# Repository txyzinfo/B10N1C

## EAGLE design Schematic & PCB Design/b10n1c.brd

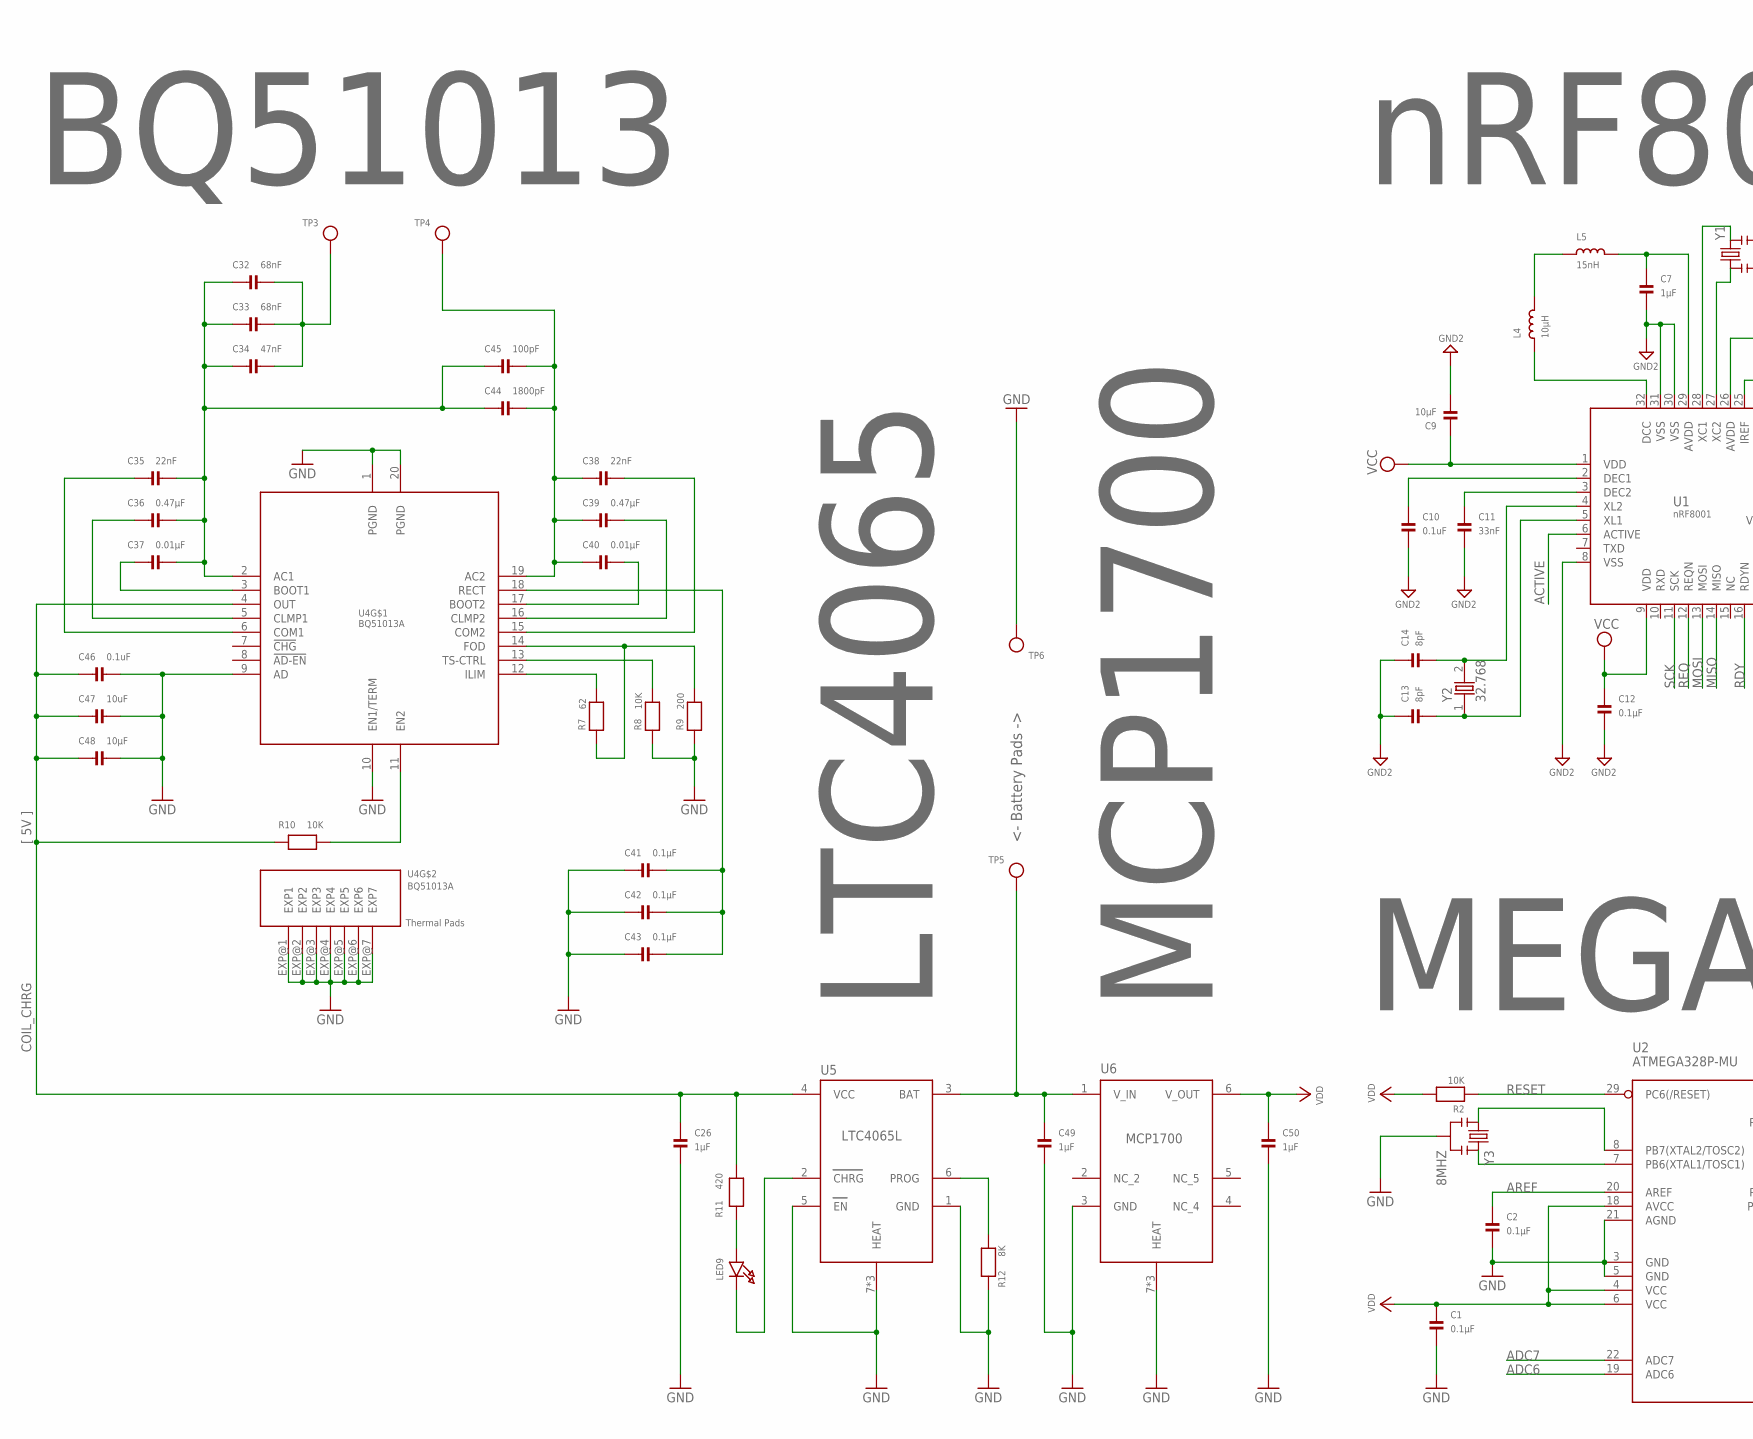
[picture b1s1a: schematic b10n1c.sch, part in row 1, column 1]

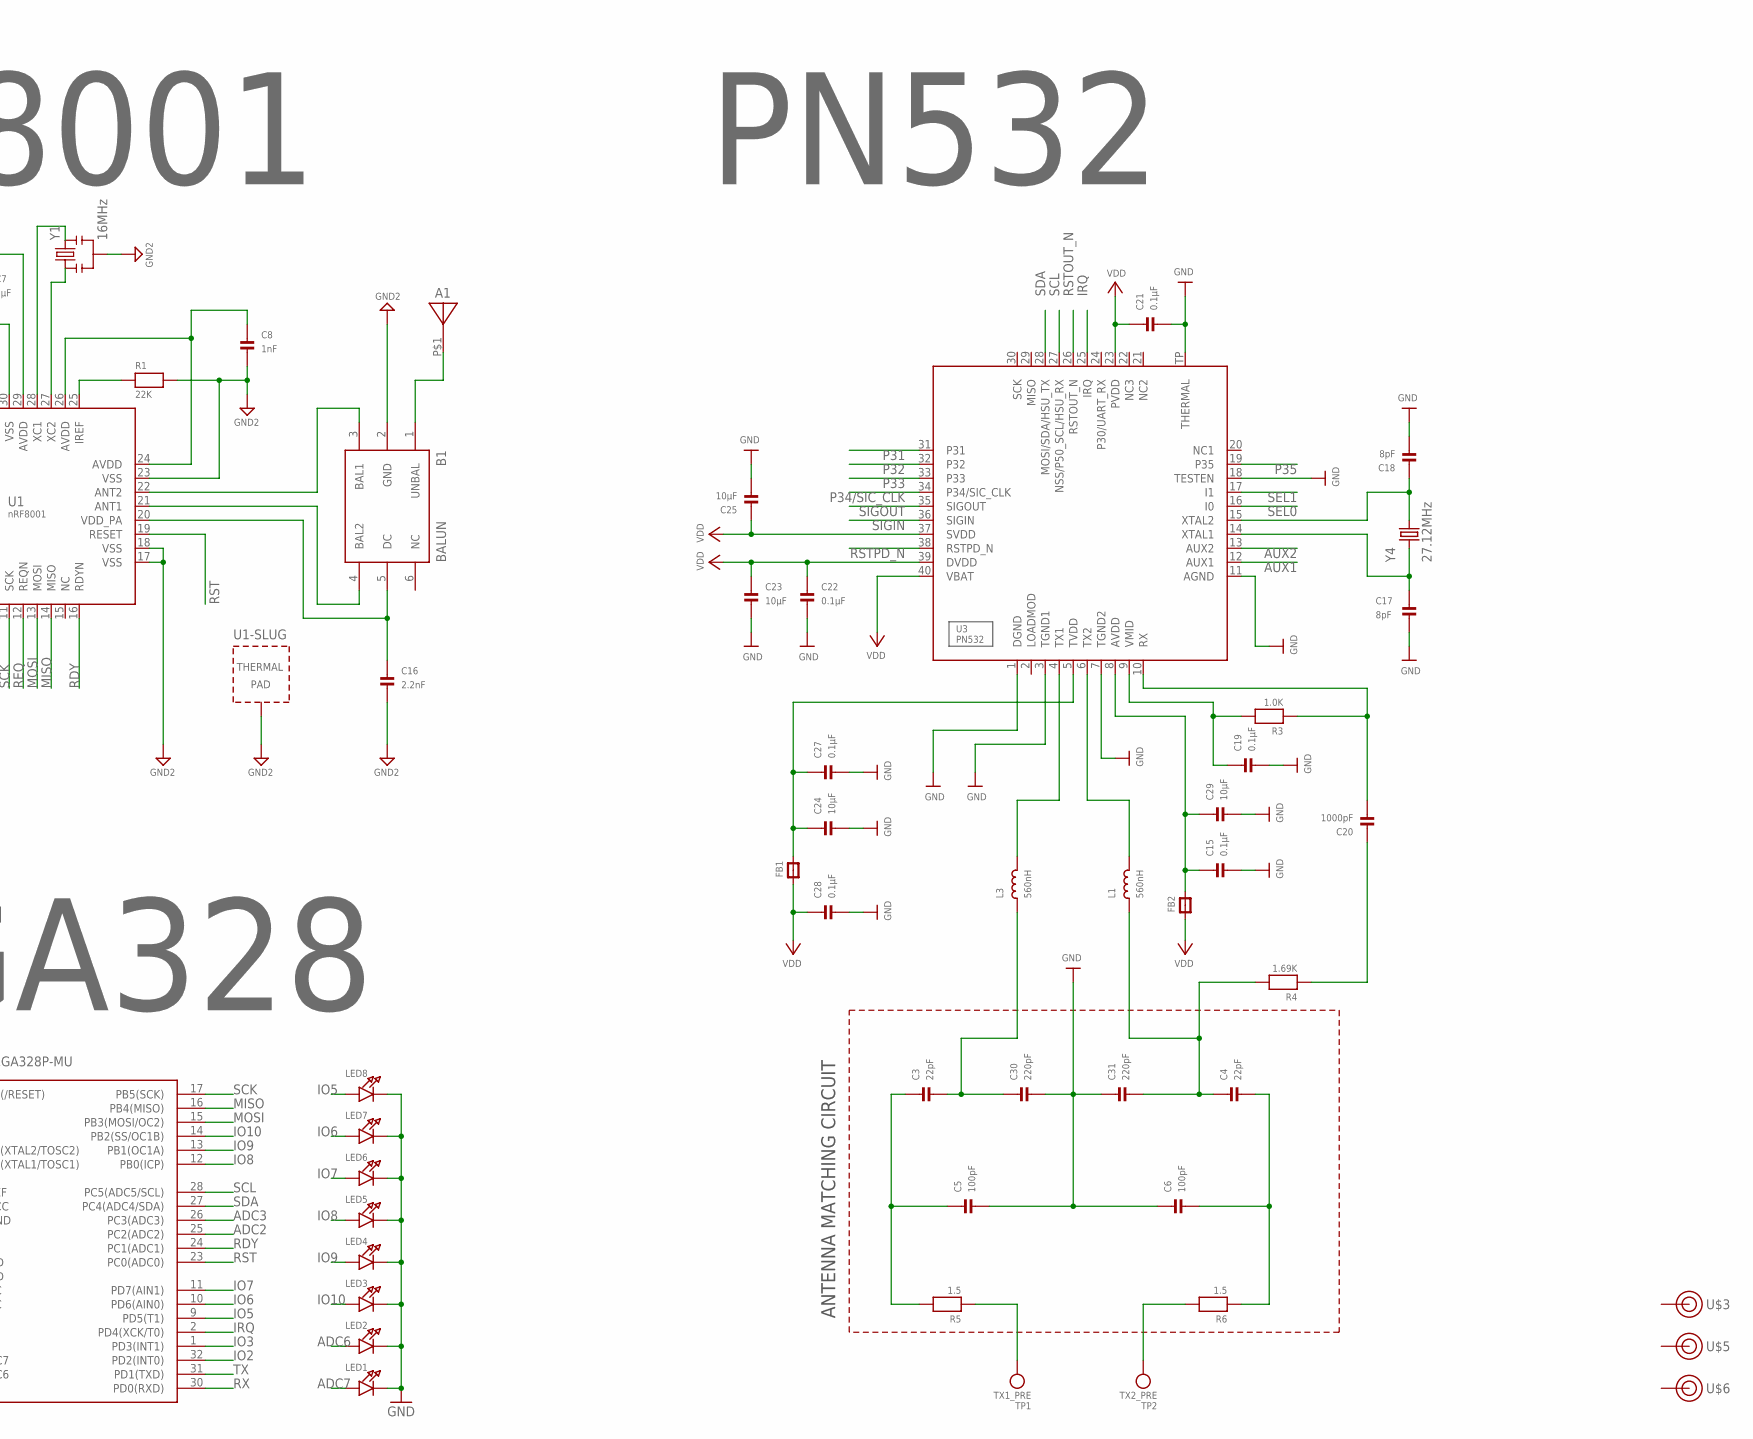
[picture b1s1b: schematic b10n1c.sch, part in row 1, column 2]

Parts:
A1: 2450AT18A100
B1: 2450BM14A0002T
C1, C2, C12, C15, C19, C21, C22, C27, C28, C41, C42, C43: 0.1µF; _0402MP
C3, C4: 22pF; _0402MP
C5, C6, C45: 100pF; _0402MP
C7, C26, C49, C50: 1µF; _0402MP
C8: 1nF; _0402MP
C9, C23, C24, C25, C29, C48: 10µF; _0402MP
C10, C46: 0.1uF; _0402MP
C11: 33nF; _0402MP
C13, C14: 8pF; _0402MP; DIGIKEY 490-5880-1-ND
C16: 2.2nF; _0402MP
C17, C18: 8pF; _0402MP
C20: 1000pF; _0402MP
C30, C31: 220pF; _0402MP
C32, C33: 68nF; _0402MP
C34: 47nF; _0402MP
C35, C38: 22nF; _0402MP
C36, C39: 0.47µF; _0402MP
C37, C40: 0.01µF; _0402MP
C44: 1800pF; _0402MP
C47: 10uF; _0402MP
FB1, FB2: FERRITE_0402MP; _0402MP
L1, L3: 560nH; _0402MP
L4: 10µH; _0603MP
L5: 15nH; _0402MP; DIGIKEY 712-1408-1-ND
LED1, LED2, LED3, LED4, LED5, LED6, LED7, LED8, LED9: LED0603_NOOUTLINE; CHIPLED_0603_NOOUTLINE
R1: 22K; _0402MP
R2, R8, R10: 10K; _0402MP
R3: 1.0K; _0402MP
R4: 1.69K; _0402MP
R5, R6: 1.5; _0402MP
R7: 62; _0402MP
R9: 200; _0402MP
R11: 420; _0402MP
R12: 8K; _0402MP
TP1: TX1_PRE; TESTPOINT_ROUND_1MM
TP2: TX2_PRE; TESTPOINT_ROUND_1MM
TP3, TP4, TP5, TP6: TESTPOINTROUND1MM; TESTPOINT_ROUND_1MM
U1: nRF8001; QFN32_5MM
U2: ATMEGA328P-MU; MLF32-M1-A
U3: PN532; HVQFN40-6X6
U4: BQ51013A; RHL_R-VQFN-N20
U5: LTC4065L
U6: MCP1700
U$3, U$5, U$6: MAKE-UB312-MICRO
Y1: 16MHz; RESONATOR-SMD
Y2: 32.768; CRYSTAL-2PIN; DIGIKEY 535-11897-1-ND
Y3: 8MHZ; RESONATOR-SMD; DIGIKEY 490-1195-1-ND
Y4: 27.12MHz; CRYSTAL-MURATA-XRCGB27M120F3M00R0; DIGIKEY 490-5581-6-ND

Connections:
AC: B1.2 (GND), C7.2, C8.2, C9.2, C10.2, C11.2, C12.2, C13.1, C14.1, C16.2, R1.2, U1.8 (VSS), U1.17 (VSS), U1.18 (VSS), U1.23 (VSS), U1.30 (VSS), U1.31 (VSS), U1.33 (TP), Y1.2
AC1: C32.2, C33.2, C34.2, TP3.P$1
AC2: C38.1, C39.1, C40.1, C44.2, C45.2, TP4.P$1, U4.19 (AC2)
ACTIVE: U1.6 (ACTIVE)
ADC2: U2.25 (PC2(ADC2))
ADC3: U2.26 (PC3(ADC3))
ADC6: LED2.A, U2.19 (ADC6)
ADC7: LED1.A, U2.22 (ADC7)
AREF: C2.1, U2.20 (AREF)
AUX1: U3.12 (AUX1)
AUX2: U3.13 (AUX2)
COIL_CHRG: C26.1, C46.1, C47.1, C48.1, R10.2, R11.1, U4.4 (OUT), U5.4 (VCC)
GND: C1.2, C2.2, C5.2, C6.1, C15.2, C17.2, C18.2, C19.2, C21.2, C22.2, C23.2, C24.2, C25.2, C26.2, C27.2, C28.2, C29.2, C30.2, C31.1, C41.1, C42.1, C43.1, C46.2, C47.2, C48.2, C49.2, C50.2, LED1.C, LED2.C, LED3.C, LED4.C, LED5.C, LED6.C, LED7.C, LED8.C, R8.1, R9.1, R12.2, TP6.P$1, U2.3 (GND), U2.5 (GND), U2.21 (AGND), U3.1 (DGND), U3.3 (TGND1), U3.7 (TGND2), U3.11 (AGND), U3.18 (TESTEN), U3.TP (THERMAL), U4.1 (PGND), U4.9 (AD), U4.10 (EN1/TERM), U4.20 (PGND), U4.EXP@1 (EXP1), U4.EXP@2 (EXP2), U4.EXP@3 (EXP3), U4.EXP@4 (EXP4), U4.EXP@5 (EXP5), U4.EXP@6 (EXP6), U4.EXP@7 (EXP7), U5.1 (GND), U5.5 (EN), U5.7 (HEAT), U5.71 (HEAT), U5.72 (HEAT), U6.3 (GND), U6.7 (HEAT), U6.71 (HEAT), U6.72 (HEAT), Y3.2
IO2: U2.32 (PD2(INT0))
IO3: U2.1 (PD3(INT1))
IO5: LED8.A, U2.9 (PD5(T1))
IO6: LED7.A, U2.10 (PD6(AIN0))
IO7: LED6.A, U2.11 (PD7(AIN1))
IO8: LED5.A, U2.12 (PB0(ICP))
IO9: LED4.A, U2.13 (PB1(OC1A))
IO10: LED3.A, U2.14 (PB2(SS/OC1B))
IRQ: U2.2 (PD4(XCK/T0)), U3.25 (IRQ)
MISO: U1.14 (MISO), U2.16 (PB4(MISO))
MOSI: U1.13 (MOSI), U2.15 (PB3(MOSI/OC2))
unnamed: B1.5 (DC), C16.1, U1.20 (VDD_PA)
unnamed: C7.1, L5.2, U1.29 (AVDD)
unnamed: C8.1, U1.24 (AVDD), U1.26 (AVDD)
unnamed: U2.7 (PB6(XTAL1/TOSC1)), Y3.3
unnamed: L4.2, L5.1
unnamed: U2.8 (PB7(XTAL2/TOSC2)), Y3.1
unnamed: C11.1, U1.3 (DEC2)
unnamed: C10.1, U1.2 (DEC1)
unnamed: U1.28 (XC1), Y1.3
unnamed: U1.27 (XC2), Y1.1
unnamed: L4.1, U1.32 (DCC)
unnamed: R1.1, U1.25 (IREF)
unnamed: L3.2, U3.4 (TX1)
unnamed: B1.4 (BAL2), U1.21 (ANT1)
unnamed: B1.3 (BAL1), U1.22 (ANT2)
unnamed: A1.P$1, B1.1 (UNBAL)
unnamed: L1.2, U3.6 (TX2)
unnamed: C3.2, C30.1, L3.1
unnamed: C17.1, U3.14 (XTAL1), Y4.1
unnamed: C18.1, U3.15 (XTAL2), Y4.3 (2)
unnamed: C19.1, R3.2, U3.9 (VMID)
unnamed: C14.2, U1.4 (XL2), Y2.2
unnamed: C13.2, U1.5 (XL1), Y2.1
unnamed: C20.2, R3.1, U3.10 (RX)
unnamed: C20.1, R4.1
unnamed: C4.1, C31.2, L1.1, R4.2
unnamed: R5.1, TP1.P$1
unnamed: R6.2, TP2.P$1
unnamed: C15.1, C29.1, FB2.2, U3.8 (AVDD)
unnamed: C24.1, C27.1, FB1.2, U3.5 (TVDD)
unnamed: C32.1, C33.1, C34.1, C35.2, C36.2, C37.2, C44.1, C45.1, U4.2 (AC1)
unnamed: LED9.A, R11.2
unnamed: C40.2, U4.17 (BOOT2)
unnamed: C41.2, C42.2, C43.2, U4.18 (RECT)
unnamed: C37.1, U4.3 (BOOT1)
unnamed: C36.1, U4.5 (CLMP1)
unnamed: C35.1, U4.6 (COM1)
unnamed: C39.2, U4.16 (CLMP2)
unnamed: C38.2, U4.15 (COM2)
unnamed: R7.1, R9.2, U4.14 (FOD)
unnamed: R8.2, U4.13 (TS-CTRL)
unnamed: R10.1, U4.11 (EN2)
unnamed: R7.2, U4.12 (ILIM)
unnamed: LED9.C, U5.2 (CHRG)
unnamed: R12.1, U5.6 (PROG)
unnamed: C49.1, TP5.P$1, U5.3 (BAT), U6.1 (V_IN)
P31: U3.31
P32: U3.32
P33: U3.33
P34/SIC_CLK: U3.34 (P34/SIC_CLK)
P35: U3.19 (P35)
RDY: U1.16 (RDYN), U2.24 (PC1(ADC1))
REQ: U1.12 (REQN)
RESET: R2.1, U2.29 (PC6(/RESET))
RST: U1.19 (RESET), U2.23 (PC0(ADC0))
RSTOUT_N: U3.26 (RSTOUT_N)
RSTPD_N: U3.38 (RSTPD_N)
RX: U2.30 (PD0(RXD))
SCK: U1.11 (SCK), U2.17 (PB5(SCK))
SCL: U2.28 (PC5(ADC5/SCL)), U3.27 (NSS/P50_SCL/HSU_RX)
SDA: U2.27 (PC4(ADC4/SDA)), U3.28 (MOSI/SDA/HSU_TX)
SEL0: U3.16 (I0)
SEL1: U3.17 (I1)
SIGIN: U3.36 (SIGIN)
SIGOUT: U3.35 (SIGOUT)
TX: U2.31 (PD1(TXD))
TX1_ANTENNA: C3.1, C5.1, R5.2
TX2_ANTENNA: C4.2, C6.2, R6.1
VCC: C9.1, C12.1, U1.1 (VDD), U1.9 (VDD)
VDD: C1.1, C21.1, C22.1, C23.1, C25.1, C28.1, C50.1, FB1.1, FB2.1, R2.2, U2.4 (VCC), U2.6 (VCC), U2.18 (AVCC), U3.23 (PVDD), U3.37 (SVDD), U3.39 (DVDD), U3.40 (VBAT), U6.6 (V_OUT)

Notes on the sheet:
BALUN
nRF8001
MEGA328
ANTENNA MATCHING CIRCUIT
PN532
Thermal Pads
[ 5V ]
MCP1700
LTC4065
BQ51013
<- Battery Pads ->

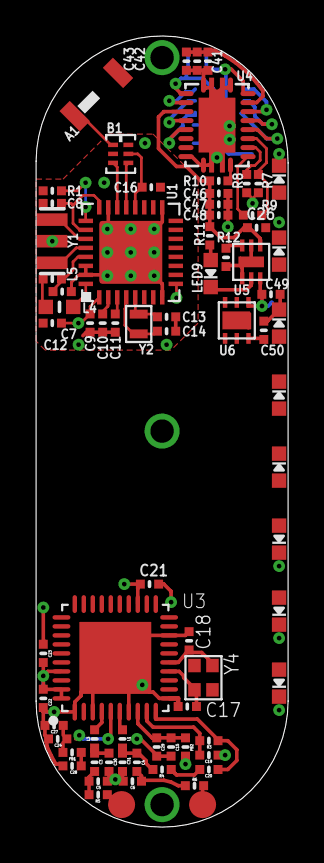
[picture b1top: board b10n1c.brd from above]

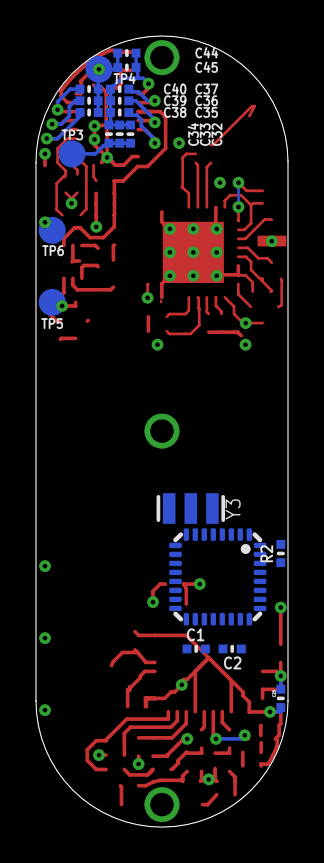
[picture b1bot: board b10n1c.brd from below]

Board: 4 copper layers, 14.0 x 43.9 mm, 98 parts (21 on the bottom side), 73 nets.

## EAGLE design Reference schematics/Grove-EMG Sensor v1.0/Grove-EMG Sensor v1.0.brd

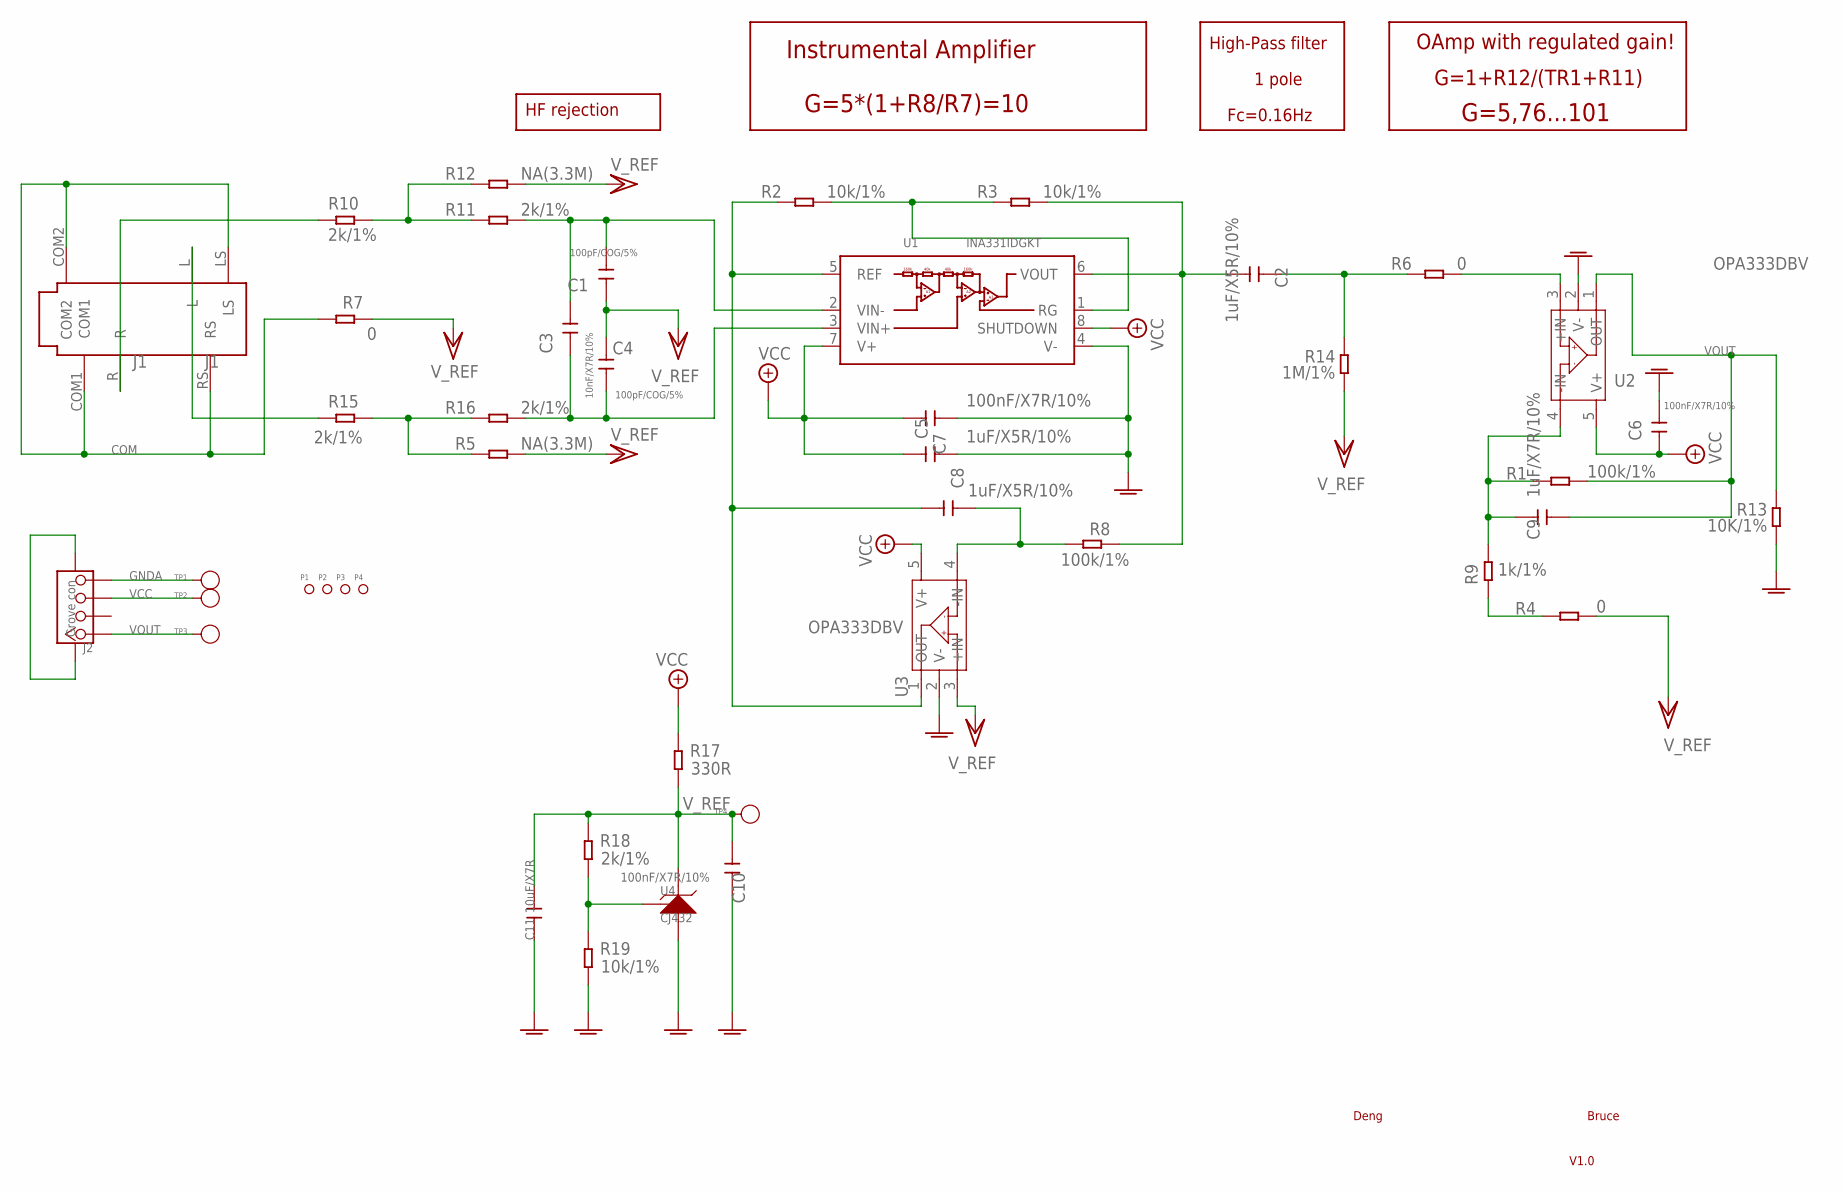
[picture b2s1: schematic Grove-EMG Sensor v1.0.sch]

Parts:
C1, C4: 100pF/COG/5%; C0603
C2, C7, C8: 1uF/X5R/10%; C0603
C3: 10nF/X7R/10%; C0603
C5, C6, C10: 100nF/X7R/10%; C0603
C9: 1uF/X7R/10%; C0603
C11: 10uF/X7R; C0805
J1: J1; 6P-SMD-3.5-NEW
J2: Grove con; 4P-SMD-2.0
P1, P2, P3, P4: PAD-MARK; ROUND-MARK-1.0
R1, R8: 100k/1%; R0603
R2, R3, R19: 10k/1%; R0603
R4, R6, R7: 0; R0603
R5, R12: NA(3.3M); R0603
R9: 1k/1%; R0603
R10, R11, R15, R16, R18: 2k/1%; R0603
R13: 10K/1%; R0603
R14: 1M/1%; R0603
R17: 330R; R0603
TP1: TP1; TP_4545
TP2: TP2; TP_4545
TP3: TP3; TP_4545
TP4: TP4; TP_4545
U1: INA331IDGKT; MSOP-8
U2, U3: OPA333DBV; SOT23-5
U4: CJ432; SOT23

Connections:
COM: J1.COM1, J1.COM2, J1.LS, J1.RS, R7.1
GNDA: C5.2, C6.1, C7.2, C10.2, C11.1, J2.4, R13.2, R19.1, TP1.T, U1.4 (V-), U2.2 (V-), U3.2 (V-), U4.3 (A)
unnamed: R4.1, R9.2
unnamed: C8.1, R8.1, U3.4 (-IN)
unnamed: J1.R, R10.1
unnamed: J1.L, R15.1
unnamed: R10.2, R11.2, R12.2
unnamed: R5.2, R15.2, R16.2
unnamed: C8.2, R2.2, U1.5 (REF), U3.1 (OUT)
unnamed: R2.1, R3.2, U1.1 (RG)
unnamed: C2.2, R6.2, R14.1
unnamed: R18.1, R19.2, U4.1 (R)
unnamed: C2.1, R3.1, R8.2, U1.6 (VOUT)
unnamed: C3.1, C4.1, R16.1, U1.3 (VIN+)
unnamed: C1.2, C3.2, R11.1, U1.2 (VIN-)
unnamed: R6.1, U2.3 (+IN)
unnamed: C9.1, R1.1, R9.1, U2.4 (-IN)
VCC: C5.1, C6.2, C7.1, J2.3, R17.2, TP2.T, U1.7 (V+), U1.8 (SHUTDOWN), U2.5 (V+), U3.5 (V+)
VOUT: C9.2, J2.1, R1.2, R13.1, TP3.T, U2.1 (OUT)
V_REF: C1.1, C4.2, C10.1, C11.2, J2.SS1, J2.SS2, R4.2, R5.1, R7.2, R12.1, R14.2, R17.1, R18.2, TP4.T, U3.3 (+IN), U4.2 (K)

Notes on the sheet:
G=1+R12/(TR1+R11)
G=5,76...101
Fc=0.16Hz
HF rejection
High-Pass filter
OAmp with regulated gain!
1 pole
G=5*(1+R8/R7)=10
Instrumental Amplifier
Deng
Bruce
V1.0

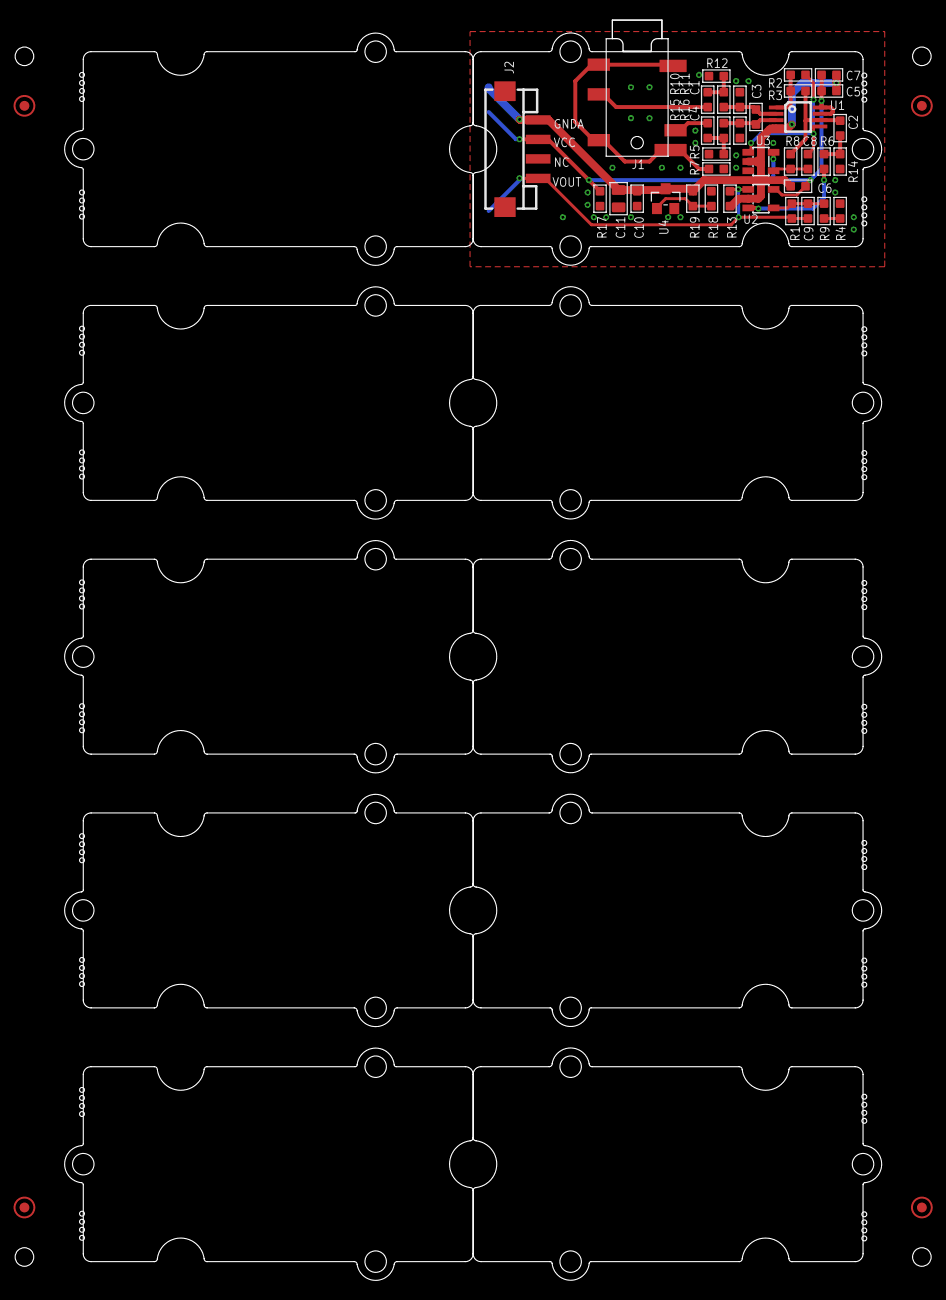
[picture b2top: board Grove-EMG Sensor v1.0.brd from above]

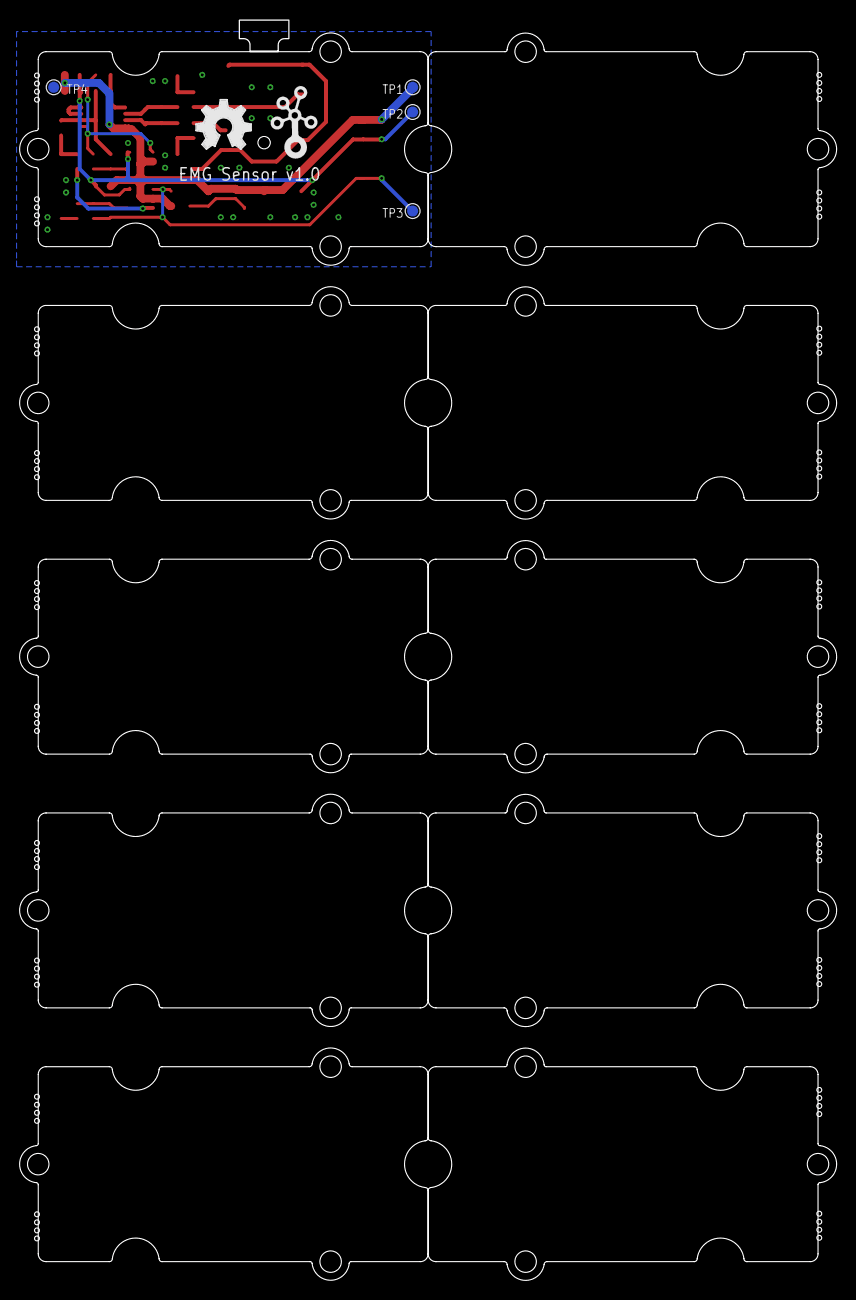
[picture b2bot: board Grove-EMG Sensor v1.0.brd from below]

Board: 2 copper layers, 83.8 x 129.3 mm, 56 parts (6 on the bottom side), 20 nets.

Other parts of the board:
U$2, U$5, U$6, U$7, U$8, U$9, U$10, U$11, U$12, U$13: GROVE-TEST-PLATFORM
U$3: OSHW_FILLX200_NOTEXT
U$4: TWIGLOGO

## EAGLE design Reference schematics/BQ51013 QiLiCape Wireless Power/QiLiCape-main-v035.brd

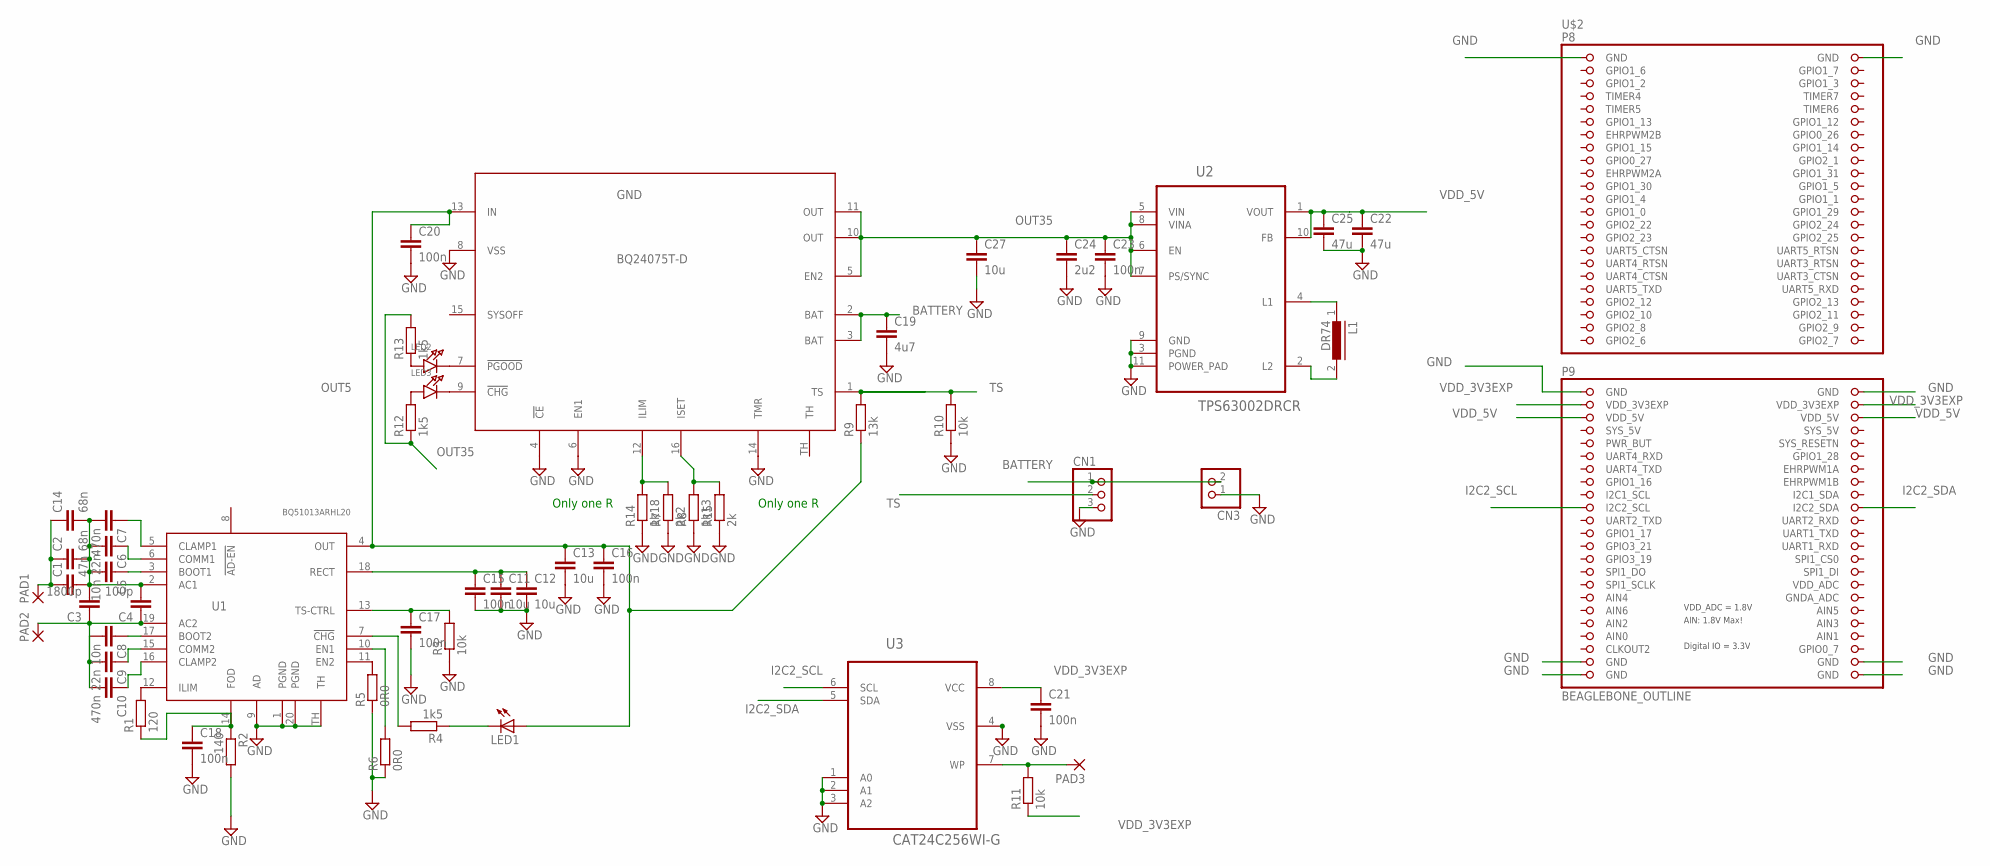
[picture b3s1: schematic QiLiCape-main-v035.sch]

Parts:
C1: 47n; C0603K
C2, C14: 68n; C0603K
C3: 1800p; C0603K
C4: 100p; C0603K
C5, C8: 10n; C0603K
C6, C9: 22n; C0603K
C7, C10: 470n; C0603K
C11, C12, C13: 10u; C1206
C15: 100n; C0805K
C16, C17, C18, C20: 100n; C0603K
C19: 4u7; C0805K
C21: 100n; C0402K
C22: 47u; C1206K
C23: 100n; C0603
C24: 2u2; C0805K
C25: 47u; C1812K
C27: 10u; C1206K
CN1: JST_3PIN; JSTPH3
CN3: JST_2PIN; JSTPH2
GND: BQ24075T-D; QFN16-3
L1: DR74
LED1: LEDSML0805; SML0805
LED2, LED3: LED0603; CHIPLED_0603
PAD1: 2,54/1,0
PAD2: 2,54/1,1
PAD3: SMD2; SMD1,27-2,54
R1: 120; R0603
R2: 140; R0603
R3, R10: 10k; R0603
R4, R12, R13: 1k5; R0603
R5, R6: 0R0; R0805
R7: 2k2; R0603
R8: 1k13; R0603
R9: 13k; R0603
R11: 10k; R0402
R14: 1k18; R0603
R15: 2k; R0603
U1: BQ51013ARHL20; RHL
U2: TPS63002DRCR; SON50P300X300X100-11N
U3: CAT24C256WI-G; SOIC127P600X175-8N
U$2: BEAGLEBONE_OUTLINE; BEAGLEBONE_SHIELD

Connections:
AC1: C1.2, C2.2, C3.2, C4.2, C5.2, C6.2, C7.2, C14.2, U1.2 (AC1)
AC1-1: C1.1, C2.1, C14.1, PAD1.1
AC2: C3.1, C4.1, C8.2, C9.2, C10.2, PAD2.1, U1.19 (AC2)
BATTERY: C19.1, CN1.1, CN3.2, GND.2 (BAT), GND.3 (BAT)
GND: C11.2, C12.2, C13.2, C15.2, C16.2, C17.2, C18.2, C19.2, C20.2, C21.2, C22.2, C23.2, C24.2, C25.2, C27.2, CN1.3, CN3.1, GND.4 (!CE), GND.6 (EN1), GND.8 (VSS), GND.14 (TMR), R2.2, R3.1, R5.1, R6.1, R7.1, R8.1, R10.1, R14.1, R15.1, U1.1 (PGND), U1.9 (AD), U1.20 (PGND), U1.TH, U2.3 (PGND), U2.9 (GND), U2.11 (POWER_PAD), U3.1 (A0), U3.2 (A1), U3.3 (A2), U3.4 (VSS), U$2.1 (GND), U$2.2 (GND), U$2.47 (GND), U$2.48 (GND), U$2.89 (GND), U$2.90 (GND), U$2.91 (GND), U$2.92 (GND)
GNDA_ADC: U$2.80 (GNDA_ADC)
I2C2_SCL: U3.6 (SCL), U$2.65 (I2C2_SCL)
I2C2_SDA: U3.5 (SDA), U$2.66 (I2C2_SDA)
unnamed: C11.1, C12.1, C15.1, U1.18 (RECT)
unnamed: C5.1, U1.3 (BOOT1)
unnamed: C6.1, U1.6 (COMM1)
unnamed: C7.1, U1.5 (CLAMP1)
unnamed: C8.1, U1.17 (BOOT2)
unnamed: C9.1, U1.15 (COMM2)
unnamed: C10.1, U1.16 (CLAMP2)
unnamed: C17.1, R3.2, U1.13 (TS-CTRL)
unnamed: GND.7 (!PGOOD), LED2.C
unnamed: LED1.C, R4.1
unnamed: R4.2, U1.7 (!CHG!)
unnamed: R6.2, U1.10 (EN1)
unnamed: R5.2, U1.11 (EN2)
unnamed: PAD3.1, R11.2, U3.7 (WP)
unnamed: GND.12 (ILIM), R7.2, R14.2
unnamed: GND.16 (ISET), R8.2, R15.2
unnamed: L1.1, U2.4 (L1)
unnamed: L1.2, U2.2 (L2)
unnamed: GND.9 (!CHG), LED3.C
unnamed: LED3.A, R12.2
unnamed: LED2.A, R13.1
unnamed: R1.2, U1.12 (ILIM)
unnamed: C18.1, R1.1, R2.1, U1.14 (FOD)
OUT5: C13.1, C16.1, C20.1, GND.13 (IN), LED1.A, R9.1, U1.4 (OUT)
OUT35: C23.1, C24.1, C27.1, GND.5 (EN2), GND.10 (OUT), GND.11 (OUT), R12.1, R13.2, U2.5 (VIN), U2.6 (EN), U2.7 (PS/SYNC), U2.8 (VINA)
SYS_5V: U$2.53 (SYS_5V), U$2.54 (SYS_5V)
TS: CN1.2, GND.1 (TS), R9.2, R10.2
VDD_3V3EXP: C21.1, R11.1, U3.8 (VCC), U$2.49 (VDD_3V3EXP), U$2.50 (VDD_3V3EXP)
VDD_5V: C22.1, C25.1, U2.1 (VOUT), U2.10 (FB), U$2.51 (VDD_5V), U$2.52 (VDD_5V)
VDD_ADC: U$2.78 (VDD_ADC)

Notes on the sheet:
Only one R

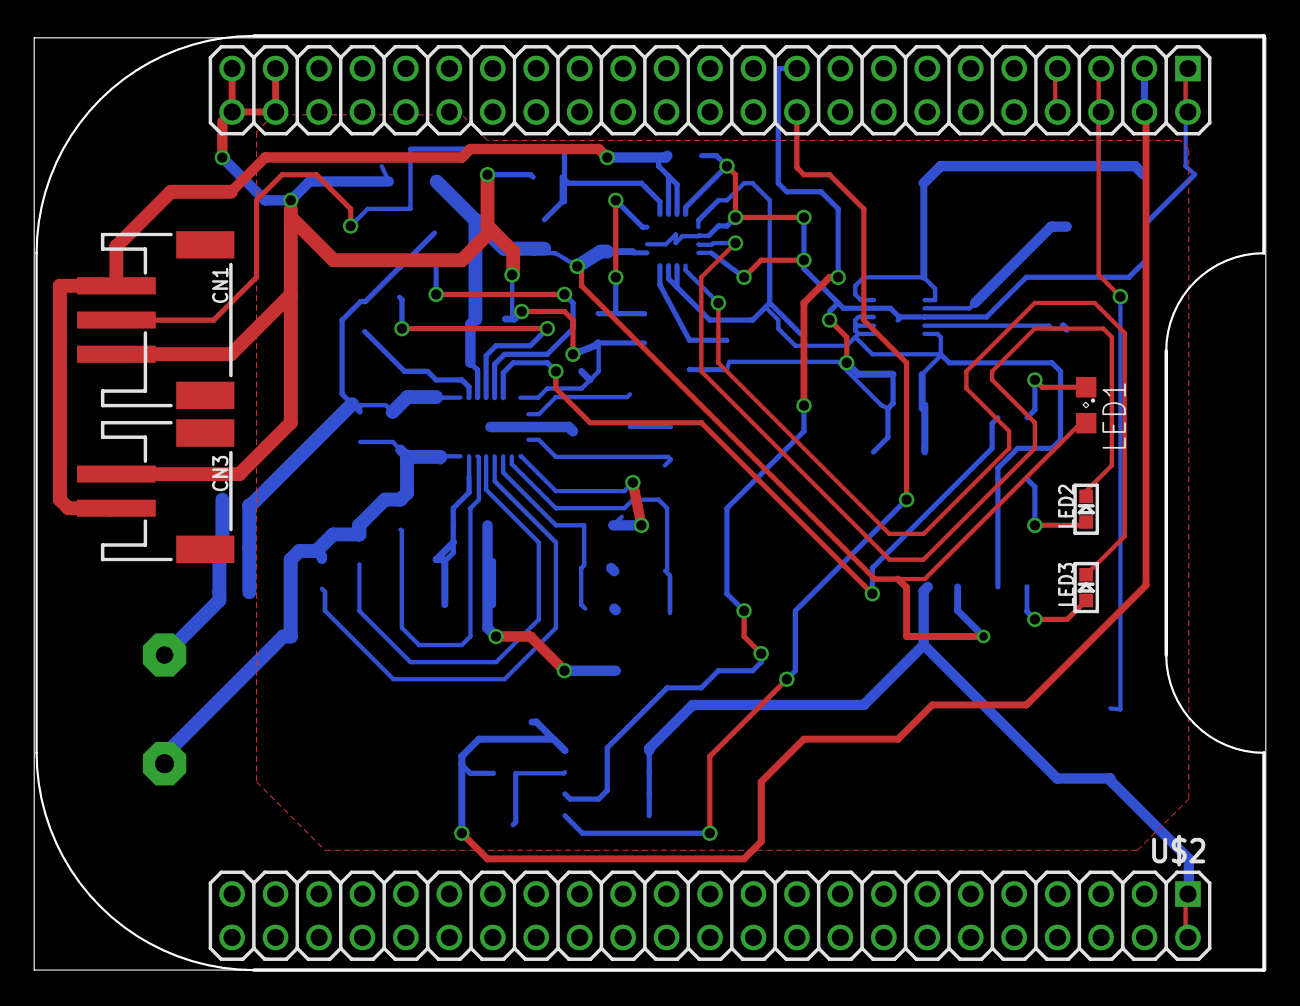
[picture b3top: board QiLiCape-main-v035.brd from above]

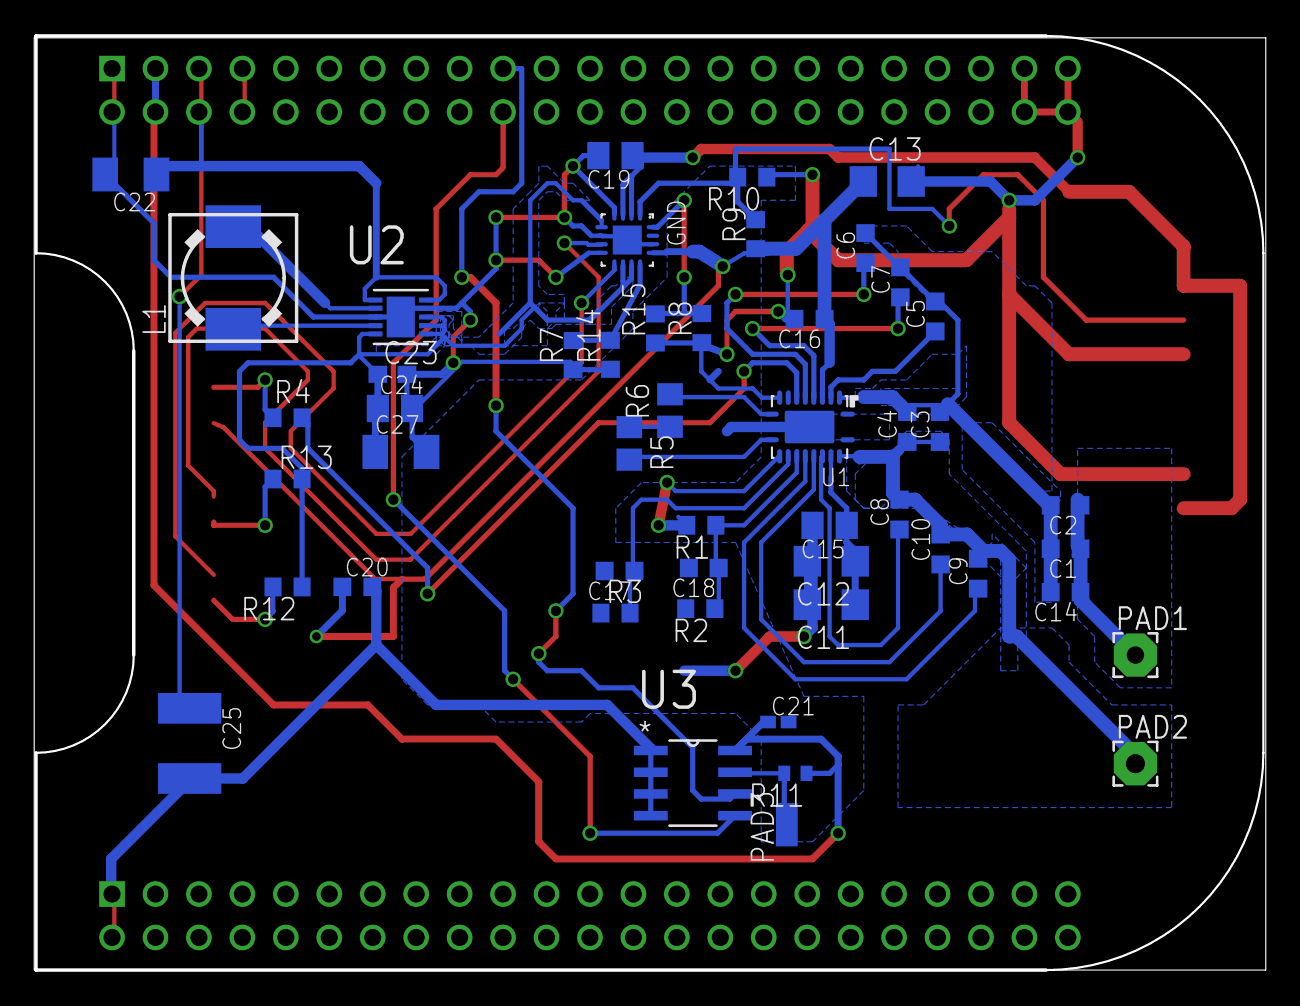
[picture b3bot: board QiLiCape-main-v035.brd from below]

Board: 2 copper layers, 72.0 x 54.5 mm, 55 parts (49 on the bottom side), 36 nets.

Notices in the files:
parts and their libraries:
microbuilder: This work is placed in the public domain, and may be freely used for commercial and non-commercial work with the following conditions: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
SparkFun-FreqCtrl: Licensing: Creative Commons ShareAlike 4.0 International - https://creativecommons.org/licenses/by-sa/4.0
